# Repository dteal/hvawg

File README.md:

# High Voltage Arbitrary Waveform Generator

This is the first draft iteration of a modular arbitrary waveform generator intended to generate possibly tens of separate ±100V 1MHz signals for small capacitive loads, e.g., electrostatic actuators or ion traps.

WARNING: THIS BOARD IS DANGEROUS. IT USES SOMEWHAT HIGH VOLTAGES AT SOMEWHAT HIGH POWER. DO NOT BUILD, TEST, OR USE WITHOUT BOTH CAUTION AND KNOWING WHAT YOU ARE DOING. No guarantees or warranty or support is provided, etc.

Specifications:
- serial data input at 3.3V or 5V up to maybe 100MHz, intended to be driven by FPGA
- 8-bit onboard DAC (with +/-1V output) (ENOB not measured but probably closer to 6 bits)
- amplifier with 100x gain gives outputs ±150V
- maximum output frequency is in the 100kHz range varying with load and voltage
- maximum designed load is tens of picofarads and megaohms of resistance
- up to four boards can be daisy-chained
- quiescent power consumption around 5 to 10W (b/c inefficient class A output stage)
- efficiency ≈1% (b/c inefficient class A output stage in open loop control)
- boards cost about $20 each and use only standard off-the-shelf parts

Measured frequency response:

(generated by feeding external signal into on-board amplifier bypassing DAC)

## Circuit Design

This circuit was made with the following constraints in mind:
- This is primarily intended to drive small capacitive loads, on the order of tens of picofarads with maybe megaohms of resistance. Note that oscilloscope input impedances are also about this much.
- Arbitrary waveform outputs between -100V and +100V and up to 1MHz. Either of those constraints is easy; together they are nontrivial. The ADHV4702 opamp can reach those voltages but only up to about 20kHz, for example.
- In order to have multiple outputs, multiple boards should be able to be daisy chained together. The final design allows up to four boards to be daisy chained and driven off a single 4-wire serial connection (three signals plus GND), for an average of 0.75 input signals per board, to drive as many boards as possible off of a single FPGA or other controller.
- Low cost. If tens of these boards are required for an application, each one should individually be cheap. This resulted in, e.g., five separate power supply inputs. The final part cost per board is around $20. Note a 2-layer PCB was used to decrease manufacturing time for external reasons; switching a 4-layer PCB or better is probably a good idea to allow better EMI mitigation techniques.
- DAC accuracy was not a priority. The original application needed less than 6 bits of resolution.
- Mass production. The circuit should not rely on manually matched transistors for a carefully-balanced amplifier. Instead, the output uses current mirrors that are cheaply implemented with off-the-shelf silicon power MOSFETs and don't require closed loop control on the output (which is not easily achieved at 1MHz at those voltages due to transistor switching time). (There is still manual tuning of amplifier gain and bias in order to minimize cost and accuracy, but this only has to be done once per board.)
- Robustness. The output can probably survive a short-circuit (untested).

The amplifier looks something like the following:

### Alternatives

Previous but insufficient approaches to similar problems include:
- Using a high-voltage op-amp, e.g., the ADHV4702 <https://www.analog.com/en/products/adhv4702-1.html>. This can achieve the +/-100V range but only up to a bit over 20kHz.
- Resonant circuits. Common in ion traps and particle accelerators, but only generate a single specific frequency.
- Discrete amplifiers of assorted topologies, e.g., <https://doi.org/10.1063/1.1988272> or <https://doi.org/10.1063/1.3622750> or <https://www.radiolocman.com/shem/schematics.html?di=637101>. Note also <https://www.falco-systems.com/High_voltage_amplifier_WMA-300.html>. Commonly used for piezoelectric actuator drives, ultrasound, MEMS, or ion traps. These amplifiers achieve the required voltage and frequency specifications but are expensive and/or complex and rely on obscure components.

### Power input

This board takes five power inputs (in addition to the GND connection, of course):
- +12V (1W)
- -12V (1W)
- +100V (5W)
- -100V (5W)
- 12V above the -100V negative rail (1W)

These should be turned on in the following order:
1. +12V
2. -12V
3. +100V
4. -100V
5. 12V above -100V rail

LEDs indicate when the three 12V power supplies are on.

The power supplies used for testing were Wanptek WPS series supplies (160V 2A and 30V 10A) from eBay.

The +/-100V high voltage supplies are used to drive the output and need to be capable of the full board power draw (potentially 10W each, depending on component selection and voltage output).

The +/-12V supplies are used to drive the DAC and intermediate amplifier opamps. These are not generated from the +/-100V because a linear regulator would be too lossy and a buck regulator would make the board significantly more complex and expensive.
Likewise, the low 12V supply is used to drive the output amplifier opamp, and is not generated from the other supplies for the same efficiency reason.

If more convenience is required, an external board can generate the 12V and 100V supplies however desired.

### DAC

The DAC circuit takes a serial input via the 74HC595 shift register and sends the output to a DAC0909 DAC chip.

The DAC is 8 bits. Four PCBs can be daisy-chained together (requiring 32 bits).

The DAC should theoretically operate up to about 100MHz, allowing four 8-bit daisy-chained boards to be updated at above 1MHz. This upper speed has not been tested yet and may be limited by inferior PCB routing.

The DAC protocol works (via the 74HC595) as follows:
- Input signals at 3.3V or 5V should both work.
- 4 pins are required (GND, store_clock, shift_clock, and serial_in).
- First, data is sent in via serial_in at each rising edge of the shift_clock.
- Next, when store_clock is brought high, the current state of the data is saved and sent to the DAC.

This should work with any 74HC595 code, e.g., many Arduino libraries.

### Level shifter

The level shifter circuit accepts an input +/-1V analog signal, translates this into a current, and sends the result to the negative high voltage rail, where it is converted back into an analog voltage to drive the output opamp.

The level shifter can be disconnected from the DAC via jumper JP3 in order to input an external analog signal (e.g., from a low-voltage waveform generator) for testing purposes.

Potentiometer RV1 controls the gain of the high voltage output and should be adjusted to give a 100x amplification.

NOTE: THE CURRENT PCB HAS AN ERROR (see "Errata" below) where the source and drain of PMOS transistor Q3 are switched. If this is not fixed during assembly, when the high voltage low rail is turned on, significant current will flow through R17, which will burn out due to excessive power draw.

### High side monitor circuit

This subcircuit provides compensation such that the final high-voltage output is independent of the high voltage supply level (i.e., high voltage inputs of +50V, +100V, and +150V should not affect a 50Vpp output signal).

Potentiometer RV2 controls the DC bias of the output and should be adjusted to center the output at GND = 0V.

Resistor R12=110kohm dissipating up to 200mW was specifically chosen to minimize power draw while also maximizing the voltage/current at the input to opamp U8A (which has nonzero input offset current).

### Output amplifier

This circuit takes an input voltage signal near the negative rail (from the level shifter) and converts this into a current signal through Q1 and R21, which form a class-A amplifier to generate the final high-voltage output. The output voltage is determined by the voltage drop of R21 with the given current.

R21 and Q1, as a class-A amplifier, form a resistive divider between the high voltage power rails, and dissipate a large (10W) current even in their quiescent state in order to drive loads with reasonable accuracy. This means they generate significant heat.

R21 was chosen at 10k as a reasonable compromise between quiescent power draw and load drive ability. R21 can be replaced with a 5kohm power resistor to draw more current but double the output load capacity.

### Output

The final output from R21 and Q1 can be connected to any one of outputs 1 through 4 via jumpers JP8 through JP11.

Four daisy-chained boards can thus be attached to separate outputs.

## Assembly and Testing

### Part choice notes

- All SMD parts are from JLCPCB and specifically chosen from parts with reliable high stock.

- Hand-soldered components were added manually afterward (not through JLCPCB) to reduce order lead time.

### Manufacturing notes

These boards were designed in KiCad and ordered from JLCPCB with help from the excellent kicad-jlc-pcb tools plugin <https://github.com/bouni/kicad-jlcpcb-tools>.

### Assembly notes

Hand assembly of the through hole components takes about 20 minutes per board.

Be sure to bend the legs of the PMOS MOSFET to switch its source and drain to fix a board error (see "Errata" section below).

Header pins are ordered in lenths of 18 to reduce costs. These should be manually cut to size (or ordered in the right size to begin with).

The power resistor R21 needs spare wires soldered on to fit the PCB footprint. The resistor hangs off the edge of the board so it can be bolted to a heatsink. It's possible these spare wires increase EMI emissions. Future board iterations could switch to a TO-220 package power resistor, matching NMOS transistor Q1, which is also at the edge of the board for easy heatsink mounting.

### Bringup notes

After the board is assembled, the following bringup/test strategy seems to work well:

- Start with jumpers JP3, JP4, and JP6 disconnected. Connect one of JP8, JP9, JP10, JP11 to choose output.
- Test DAC. Apply +12V then -12V supply (if +12V but not -12V is applied too long, DAC may heat up). Confirm LEDs light up. Add DAC input signal. Use thermal camera to confirm no major hot spots (NE5532 opamps at 35°C, LEDs at 32°C, not much else).
- Confirm DAC output is good (TP2/JP3 via oscilloscope). Full scale output is around 2.8Vpp.
- Test high voltage monitor circuit. Attach +120V supply, confirm high voltage monitor output (TP3 via multimeter) is stable and good and in the 1 to 3V range. R12 should rise in temperature (maybe 36°C) due to its 200mW power dissipation.
- Turn off power supplies and add jumpers JP3, JP6.
- Test level shifter. Apply +12V, -12V, +120V, and -120V. Confirm temperatures good (no significant change from before).
- Confirm DAC and monitor outputs remain good.
- Confirm level shifter output is sine wave (measure JP4 oscilloscope with AC coupling).
- Turn supplies off again, add jumper JP4.
- Test final output stage. Turn supplies on, including +12V on negative rail this time (additional LED should come on).
- Confirm only thermal change is output resistor and MOSFET heating to maybe 60-80°C (if supplies are +/-120V).
- Confirm final board output (measured at TP5, output port, or resistor lead via DC-coupled multimeter) is expected signal. Might be DC shifted and cut off at high/low rail.
- Adjust RV2 to center output wave at 0V.
- Adjust RV1 to set gain to get about +/-100V output. Can set to +/-128V full-scale output so that a 1 bit input change results in 1V output change.

### SMD components (JLCPCB)

| Part no.          | QTY | Cost | JLC type | Note                      | URL                                                                    |
|-------------------|-----|------|----------|---------------------------|------------------------------------------------------------------------|
| 74HC595D,118      |   1 | 0.10 | basic    | shift register            | https://jlcpcb.com/partdetail/Nexperia-74HC595D118/C5947               |
| DAC0808LCMX/NOPB  |   1 | 1.80 | extended | dac                       | https://jlcpcb.com/partdetail/TexasInstruments-DAC0808LCMXNOPB/C132006 |
| NE5532DR          |   2 | 0.15 | basic    | opamp                     | https://jlcpcb.com/partdetail/TexasInstruments-NE5532DR/C7426          |
| LM8261M5X/NOPB    |   2 | 2.12 | extended | opamp                     | https://jlcpcb.com/partdetail/TexasInstruments-LM8261M5XNOPB/C7968     |
| L78M05ABDT-TR     |   1 | 0.13 | basic    | 5V regulator              | https://jlcpcb.com/partdetail/Stmicroelectronics-L78M05ABDTTR/C58069   |
| KT-0603W          |   3 | 0.01 | basic    | white 0603 LED            | https://jlcpcb.com/partdetail/Hubei_KentoElec-KT0603W/C2290            |
| RT0402BRE072K74L  |  12 | 0.02 | extended | 2.74kohm 0402 0.1% 62.5mW | https://jlcpcb.com/partdetail/Yageo-RT0402BRE072K74L/C705647           |
| WR20X750JTL       |   1 | 0.02 | extended | 75ohm 2010 200V           | https://jlcpcb.com/partdetail/Walsin_TechCorp-WR20X750JTL/C172257      |
| 1206W4F1004T5E    |   4 | 0.01 | basic    | 1Mohm 1206 200V 250mW     | https://jlcpcb.com/partdetail/18615-1206W4F1004T5E/C17927              |
| UD2D4R7M0810      |   2 | 0.08 | extended | 4.7uF 200V SMD            | https://jlcpcb.com/partdetail/HonorElec-UD2D4R7M0810/C88701            |
| CC0603KRX7R9BB104 |  12 | 0.01 | basic    | 100nF 0603 50V            | https://jlcpcb.com/partdetail/Yageo-CC0603KRX7R9BB104/C14663           |
| CL31A106KBHNNNE   |  13 | 0.03 | basic    | 10uF 1206 50V             | https://jlcpcb.com/partdetail/14236-CL31A106KBHNNNE/C13585             |
| 2010W2J0114T4S    |   1 | 0.01 | extended | 110kohm 2010 200V 500mW   | https://jlcpcb.com/partdetail/21062-2010W2J0114T4S/C20351              |

### Through-hole components (manually added afterward)

| Part no.       | QTY | Cost  | Note                  | URL                                                                                           |
|----------------|-----|-------|-----------------------|-----------------------------------------------------------------------------------------------|
| 3296Y-1-472LF  |   2 | $1.3  | 4.7kohm trimpot       | https://www.digikey.com/en/products/detail/bourns-inc/3296Y-1-472LF/2536016                   |
| IRF9610PBF     |   1 | $1.1  | PMOS power FET        | https://www.digikey.com/en/products/detail/vishay-siliconix/IRF9610PBF/811768                 |
| IRF730PBF      |   1 | $1.1  | NMOS power FET        | https://www.digikey.com/en/products/detail/vishay-siliconix/IRF730PBF/811793                  |
| QPC02SXGN-RC   |   4 | $0.04 | jumper                | https://www.digikey.com/en/products/detail/sullins-connector-solutions/QPC02SXGN-RC/2618262   |
| THS2510KJ      |   1 | $2.5  | 10kohm power resistor | https://www.digikey.com/en/products/detail/te-connectivity-passive-product/THS2510KJ/2366983  |
| PREC018SABN-RC |   3 | $0.25 | 18-pin male header    | https://www.digikey.com/en/products/detail/sullins-connector-solutions/PREC018SABN-RC/2775036 |
| PPPC181LGBN-RC |   3 | $0.82 | 18-pin female header  | https://www.digikey.com/en/products/detail/sullins-connector-solutions/PPPC181LGBN-RC/775951  |

## Errata and Future Improvements

Board error:
- The PMOS transistor (Q3) source and drain pins are switched on the PCB. This can be fixed when hand-soldering by bending the MOSFET legs to fit the right holes. Not doing this causes excessive current through R17, burning it out, with possible additional damage to RV1.

EMI issue:
- I suspect this board might sometimes generate nontrivial RF noise. Qualitative tests show unshielded wires on the output (or maybe even the wires connecting the through-hole power resistor) generate an undesired signal. Thus, be very careful with board use. Future board iterations should fix this issue by, e.g., more careful PCB trace design and changing the signal output connector to a shielded RF SMA connector or similar.

Improvements:
- The first iteration used a 25W chassis-mount power resistor, which worked fine without heatsinking but needed manual wiring to the PCB. To avoid the inconvenience of having a component not directly mounted to the PCB, future iterations might consider using a TO-220 package power resistor and heatsinking instead (e.g., AP836 10K J, https://www.digikey.com/en/products/detail/ohmite/AP836-10K-J/5878547 ).
- A 2-layer PCB was used to decrease manufacturing time for external reasons; switching a 4-layer PCB or better is probably a good idea to allow better EMI mitigation techniques.

## Images

### 3D render

### Assembled PCBs

### Thermal testing

Note the hottest parts of the circuit are the power resistor and MOSFET near the output, as expected.

### Frequency response testing

An external function generator was used to generate test waveforms by disconnecting the DAC via jumper JP3.

### Daisychain test

### PCB frame concept

Heatsinks, external wires, and control board not included. Note a large flat heatsink is easy to add along the output power resistors and MOSFETs.

### EMI Issue

Several-foot-long unshielded wires connected to the output and a capacitive load interfere with the signal generator. Note the waveform on the oscilloscope only shows half a sinusoid; the lower half was somehow blocked. The test was immediately stopped.

Using a shielded cable reduced interference, but that's still not a perfect sinusoid on the oscilloscope. Recommendation: improve PCB to minimize external wires and other possible EMI sources and use a proper RF SMA connector for the output.

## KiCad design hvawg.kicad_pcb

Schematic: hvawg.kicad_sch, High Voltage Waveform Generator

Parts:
C1, C2, C3, C5, C9, C12, C13, C15, C22, C23, C24, C30, C31: 10u; C_1206_3216Metric
C4, C6, C7, C8, C10, C11, C14, C20, C21, C25, C28, C29: 100n; C_0603_1608Metric
C26, C27: 4.7u; CP_Elec_8x10.5
D1, D2, D3: LED; LED_0603_1608Metric
H1, H2, H3, H4: MountingHole; MountingHole_3.2mm_M3_Pad
J1, J3, J5, J7: Conn_01x04_Pin; PinSocket_1x04_P2.54mm_Horizontal_flipped
J2, J4, J6, J8: Conn_01x04_Pin; PinSocket_1x04_P2.54mm_Horizontal
J9: Conn_01x08_Pin; PinHeader_1x08_P2.54mm_Vertical
J10: Conn_01x01_Pin; PinSocket_1x01_P2.54mm_Horizontal
JP1: SolderJumper_2_Open; SolderJumper-2_P1.3mm_Open_RoundedPad1.0x1.5mm
JP2: SolderJumper_2_Bridged; SolderJumper-2_P1.3mm_Bridged_RoundedPad1.0x1.5mm
JP3, JP4, JP6: Jumper_2_Bridged; PinHeader_1x02_P2.54mm_Vertical
JP8, JP9, JP10, JP11: Jumper_2_Open; PinHeader_1x02_P2.54mm_Vertical
Q1: IRF730; TO-220-3_Vertical
Q3: IRF9610; TO-220-3_Vertical
R1, R2, R3, R4, R5, R6, R7, R8, R9, R10, R11, R17: 2.7k; R_0402_1005Metric
R12: 110k; R_2010_5025Metric
R15, R18, R24, R25: 1M; R_1206_3216Metric
R19, R23: 100; R_Axial_DIN0207_L6.3mm_D2.5mm_P2.54mm_Vertical; not fitted
R21: 10k; R_Axial_Power_L25.0mm_W9.0mm_P10.16mm_Vertical
R22: 75; R_2010_5025Metric
RV1: 3k; Potentiometer_Bourns_3296Y_Vertical
RV2: 1k; Potentiometer_Bourns_3296Y_Vertical
TP1, TP2, TP3, TP4, TP5: TestPoint; TestPoint_Keystone_5005-5009_Compact
U1: L7805; TO-252-2
U2: 74HC595D,110; SOIC-16_3.9x9.9mm_P1.27mm
U3: DAC0808LCMX/NOPB; SOIC-16_3.9x9.9mm_P1.27mm
U4, U8: NE5532; SOIC-8_3.9x4.9mm_P1.27mm
U6, U7: LM8261; SOT-23-5

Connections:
+12V: C1.1, C10.1, C12.1, C20.1, C22.1, C28.1, C30.1, J3.3, J4.3, J9.3, R1.1, U1.1 (IN), U4.8 (V+), U6.5 (V+), U8.8 (V+)
+100V: C26.1, J5.2, J6.2, J9.6, R12.1, R21.2, R24.1
-12V: C7.1, C8.2, C9.1, C11.1, C13.1, C21.1, C23.1, C29.1, C31.1, J3.4, J4.4, J9.4, R2.2, U3.7 (VEE), U4.4 (V-), U6.2 (V-), U8.4 (V-)
-100+12V: C24.2, C25.2, J5.3, J6.3, J9.7, R3.1, R15.2, U7.5 (V+)
-100V: C24.1, C25.1, C27.2, D3.1 (K), J5.4, J6.4, J9.8, R15.1, R17.2, R18.2, R19.2, R22.2, R23.1, R25.2, U7.2 (V-)
GND: C1.2, C2.2, C3.2, C4.2, C5.2, C6.2, C7.2, C9.2, C10.2, C11.2, C12.2, C13.2, C14.2, C15.2, C20.2, C21.2, C22.2, C23.2, C26.2, C27.1, C28.2, C29.2, C30.2, C31.2, D1.1 (K), D2.2 (A), J1.1, J2.1, J3.1, J3.2, J4.1, J4.2, J5.1, J6.1, J9.1, J9.2, J9.5, J10.1, R6.2, R10.2, R24.2, R25.1, RV2.2, U1.2 (GND), U2.8 (GND), U2.13 (~OE), U3.6 (GND)
unnamed: D1.2 (A), R1.2
unnamed: D2.1 (K), R2.1
unnamed: D3.2 (A), R3.2
unnamed: J7.1, J8.1, JP8.2 (B)
unnamed: J7.2, J8.2, JP9.2 (B)
unnamed: J7.3, J8.3, JP10.2 (B)
unnamed: J7.4, J8.4, JP11.2 (B)
unnamed: JP1.1 (A), R4.2, R5.1
unnamed: C2.1, C3.1, C4.1, C5.1, C6.1, JP1.2 (B), R4.1, R7.1, TP1.1, U1.3 (OUT), U2.10 (~SRCLR), U2.16 (VCC), U3.1 (VCC)
unnamed: JP2.1 (A), R10.1
unnamed: JP2.2 (B), R9.2, U4.3 (+)
unnamed: JP3.2 (B), U6.3 (+)
unnamed: JP4.2 (B), U7.3 (+)
unnamed: JP6.1 (A), RV1.1
unnamed: JP8.1 (A), JP9.1 (A), JP10.1 (A), JP11.1 (A), Q1.2 (D), R21.1, TP5.1
unnamed: Q1.1 (G), R18.1, U7.1
unnamed: Q1.3 (S), R22.1, R23.2, U7.4 (-)
unnamed: Q3.2 (D), RV1.2, U6.4 (-)
unnamed: Q3.1 (G), U6.1
unnamed: R7.2, R8.1
unnamed: R8.2, R9.1
unnamed: U2.15 (QA), U3.16 (A8)
unnamed: U2.1 (QB), U3.15 (A7)
unnamed: U2.2 (QC), U3.14 (A6)
unnamed: U2.3 (QD), U3.13 (A5)
unnamed: U2.4 (QE), U3.12 (A4)
unnamed: U2.5 (QF), U3.11 (A3)
unnamed: U2.6 (QG), U3.10 (A2)
unnamed: U2.7 (QH), U3.9 (A1)
unnamed: C8.1, U3.4 (COMPEN)
unnamed: R5.2, U3.2 (VREF+)
unnamed: R6.1, U3.3 (VREF-)
unnamed: R11.1, U4.1, U4.2 (-)
unnamed: C14.1, C15.1, R12.2, RV2.1, U8.3 (+)
dac_out: JP3.1 (A), R11.2, TP2.1, U3.8 (I0)
levelshift_out: JP4.1 (A), Q3.3 (S), R17.1, R19.1, TP4.1
monitor_out: JP6.2 (B), TP3.1, U8.1, U8.2 (-)
serial_in: J1.2, U2.14 (SER)
serial_out: J2.2, U2.9 (QH')
shift_clock: J1.3, J2.3, U2.11 (SRCLK)
store_clock: J1.4, J2.4, U2.12 (RCLK)

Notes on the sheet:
Vds_max > 300V rise/fall < 500ns 10W or greater small gate cap
Level shifter
LM8261M5X/NOPB > 20MHz GBWP high cap drive supply range > 10V
100x divider Choose divider to minimize power but also have greater current than NE5532 bias current (~500nA)
provided via external supply; opamp draws up to 0.1W so linear regulation from >100V is inefficient
average 0.1k (for 5k) or 2.8k (for 10k out) adjust 0-4.7k
1k average adjust 0 to 4.7k (coarse adjust)
use generic 0603 SMD LEDs assume 5-10mA current draw use 1k-3k resistors
L78M05ABDT-TR
Use this to determine amplifier gain Mirror gives ~50x This should be ~2x So adjust resistor to about half of Rout, i.e., 2.5 to 5kohm. Also needs sufficient precision to get <0.5% (1 LSB)
Power
thru-hole, just in case
note NE552DR has low slew rate can handle maybe 2.5Vpp max at 1MHz
in case I need a gate resistor
1:4 voltage divider (1.25V output)
5V regulator - makes 74HC595 both fast and able to receive 3.3V inputs - only needs ~10% accuracy as long as it is stable/precise (amplifier gain can be used to compensate) - probably want 1W part?
> 200V
for cable ground shield
larger than MOSFET gate
power resistor 10W or greater
set gate=0V if opamp off
bleed resistors > 200V
DAC
Dissipates ~200mW so use 1W package!
High side monitor
choose value so mirror amplification is a bit less than 50x. also use max current possible w/o excessive power dissipation, to reduce errors from opamp bias current 10k Rout -> max 600uA, average 300uA 5k Rout -> max 1200uA, average 600uA LM8261 bias current is ~1uA (and there are two), so set 1 LS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
output constant 1.25V
Mechanical
matched resistors
10k Rout -> max 30mA, average 15mA 5k Rout -> max 60mA, average 30mA set control voltage ~=1V to keep R_mirror_out < 100mW
tie to negative rail if supply disconnects
Amplifier
need 2.5k to 5k ohm total (for 5k or 10k Rout) (with 55:1 ratio: need 2.7k-5.5kohm)

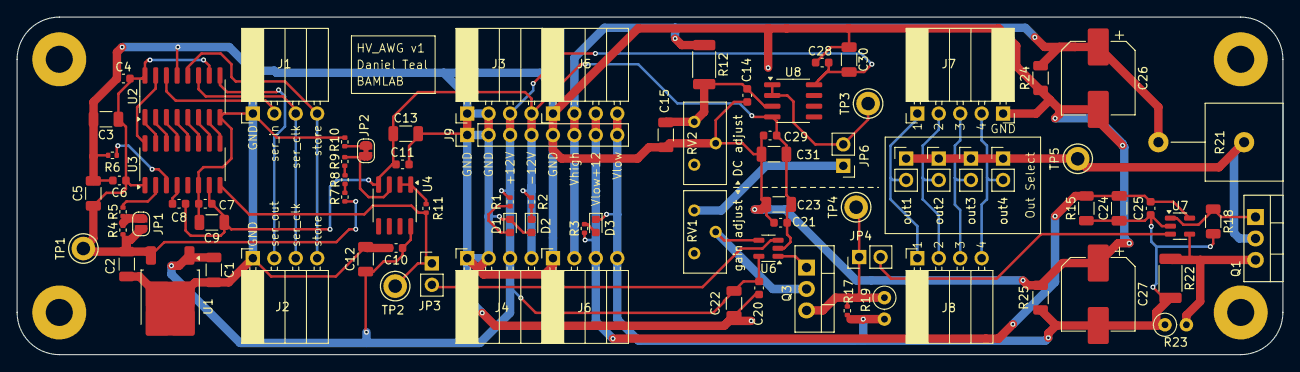
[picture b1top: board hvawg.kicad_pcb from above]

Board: 2 copper layers, 150.0 x 40.0 mm, 90 parts (0 on the bottom side), 47 nets.

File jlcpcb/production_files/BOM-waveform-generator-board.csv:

Comment,Designator,Footprint,LCSC
DAC0808LCMX/NOPB,U3,SOIC-16_3.9x9.9mm_P1.27mm,C132006
10u,"C1,C12,C13,C15,C2,C22,C23,C24,C3,C30,C31,C5,C9",C_1206_3216Metric,C13585
100n,"C10,C11,C14,C20,C21,C25,C28,C29,C4,C6,C7,C8",C_0603_1608Metric,C14663
75,R22,R_2010_5025Metric,C172257
1M,"R15,R18,R24,R25",R_1206_3216Metric,C17927
110k,R12,R_2010_5025Metric,C20351
LED,"D1,D2,D3",LED_0603_1608Metric,C2290
L7805,U1,TO-252-2,C58069
"74HC595D,110",U2,SOIC-16_3.9x9.9mm_P1.27mm,C5947
2.7k,"R1,R10,R11,R17,R2,R3,R4,R5,R6,R7,R8,R9",R_0402_1005Metric,C705647
NE5532,"U4,U8",SOIC-8_3.9x4.9mm_P1.27mm,C7426
LM8261,"U6,U7",SOT-23-5,C7968
4.7u,"C26,C27",CP_Elec_8x10.5,C88701

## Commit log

2024-08-29 Initial upload
2024-08-29 add datasheets
2024-08-29 Add initial JLCPCB files
2024-08-29 Added BOM
2024-08-29 README updates
2024-08-29 Add README details and images
2024-08-29 Typo fix
2024-08-29 Added circuit to README
2024-08-29 Add gitignore
2024-08-29 Add PCB layer info
2024-08-29 Add LTSpice simulations
2024-08-29 Add assembly details
2024-08-29 Add manufacturing notes
2024-08-29 Add power supply source note
2024-08-29 Add 3D models
2024-08-29 Added specifications
2024-08-29 Add efficiency notes
2024-08-29 Add economic notes
2024-08-29 Add load rating
2024-08-29 Add bringup procedure
2024-08-29 Clarify section
2024-08-29 Clarify draft status
2024-09-21 Added simple Arduino test script. Generates waves up to ~20Hz.
